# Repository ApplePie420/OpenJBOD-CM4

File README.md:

# Raspberry Pi CM4 OpenJBOD Controller

This project is heavily inspired by the work of [TheGuyDanish](https://github.com/openjbod/rp2040), specifically his [OpenJBOD](https://github.com/OpenJBOD) thingamajig.

It aims to provide much more "hackable" and robust way to to what OpenJBOD aims to do.

You can preview the schematics [in .pdf here](docs/CM4_JBOD_Control_Board.pdf)

## Images

# KiCAD libraries

Since I am not sure how to properly export my global libraries to the project, and I am too lazy to be bothered by changing the references individually, I have provided the entire "Custom_Libs" folder that I have on my computer. Some footprints or whatever might not be used in this project, you can safely ignore those. Adding this folder to library path should be enough for KiCAD to then locate all necessary symbols, footprints and 3D models. If not, you can link them manually. I might fix this sometime in the future maybe.

--- TBA ---

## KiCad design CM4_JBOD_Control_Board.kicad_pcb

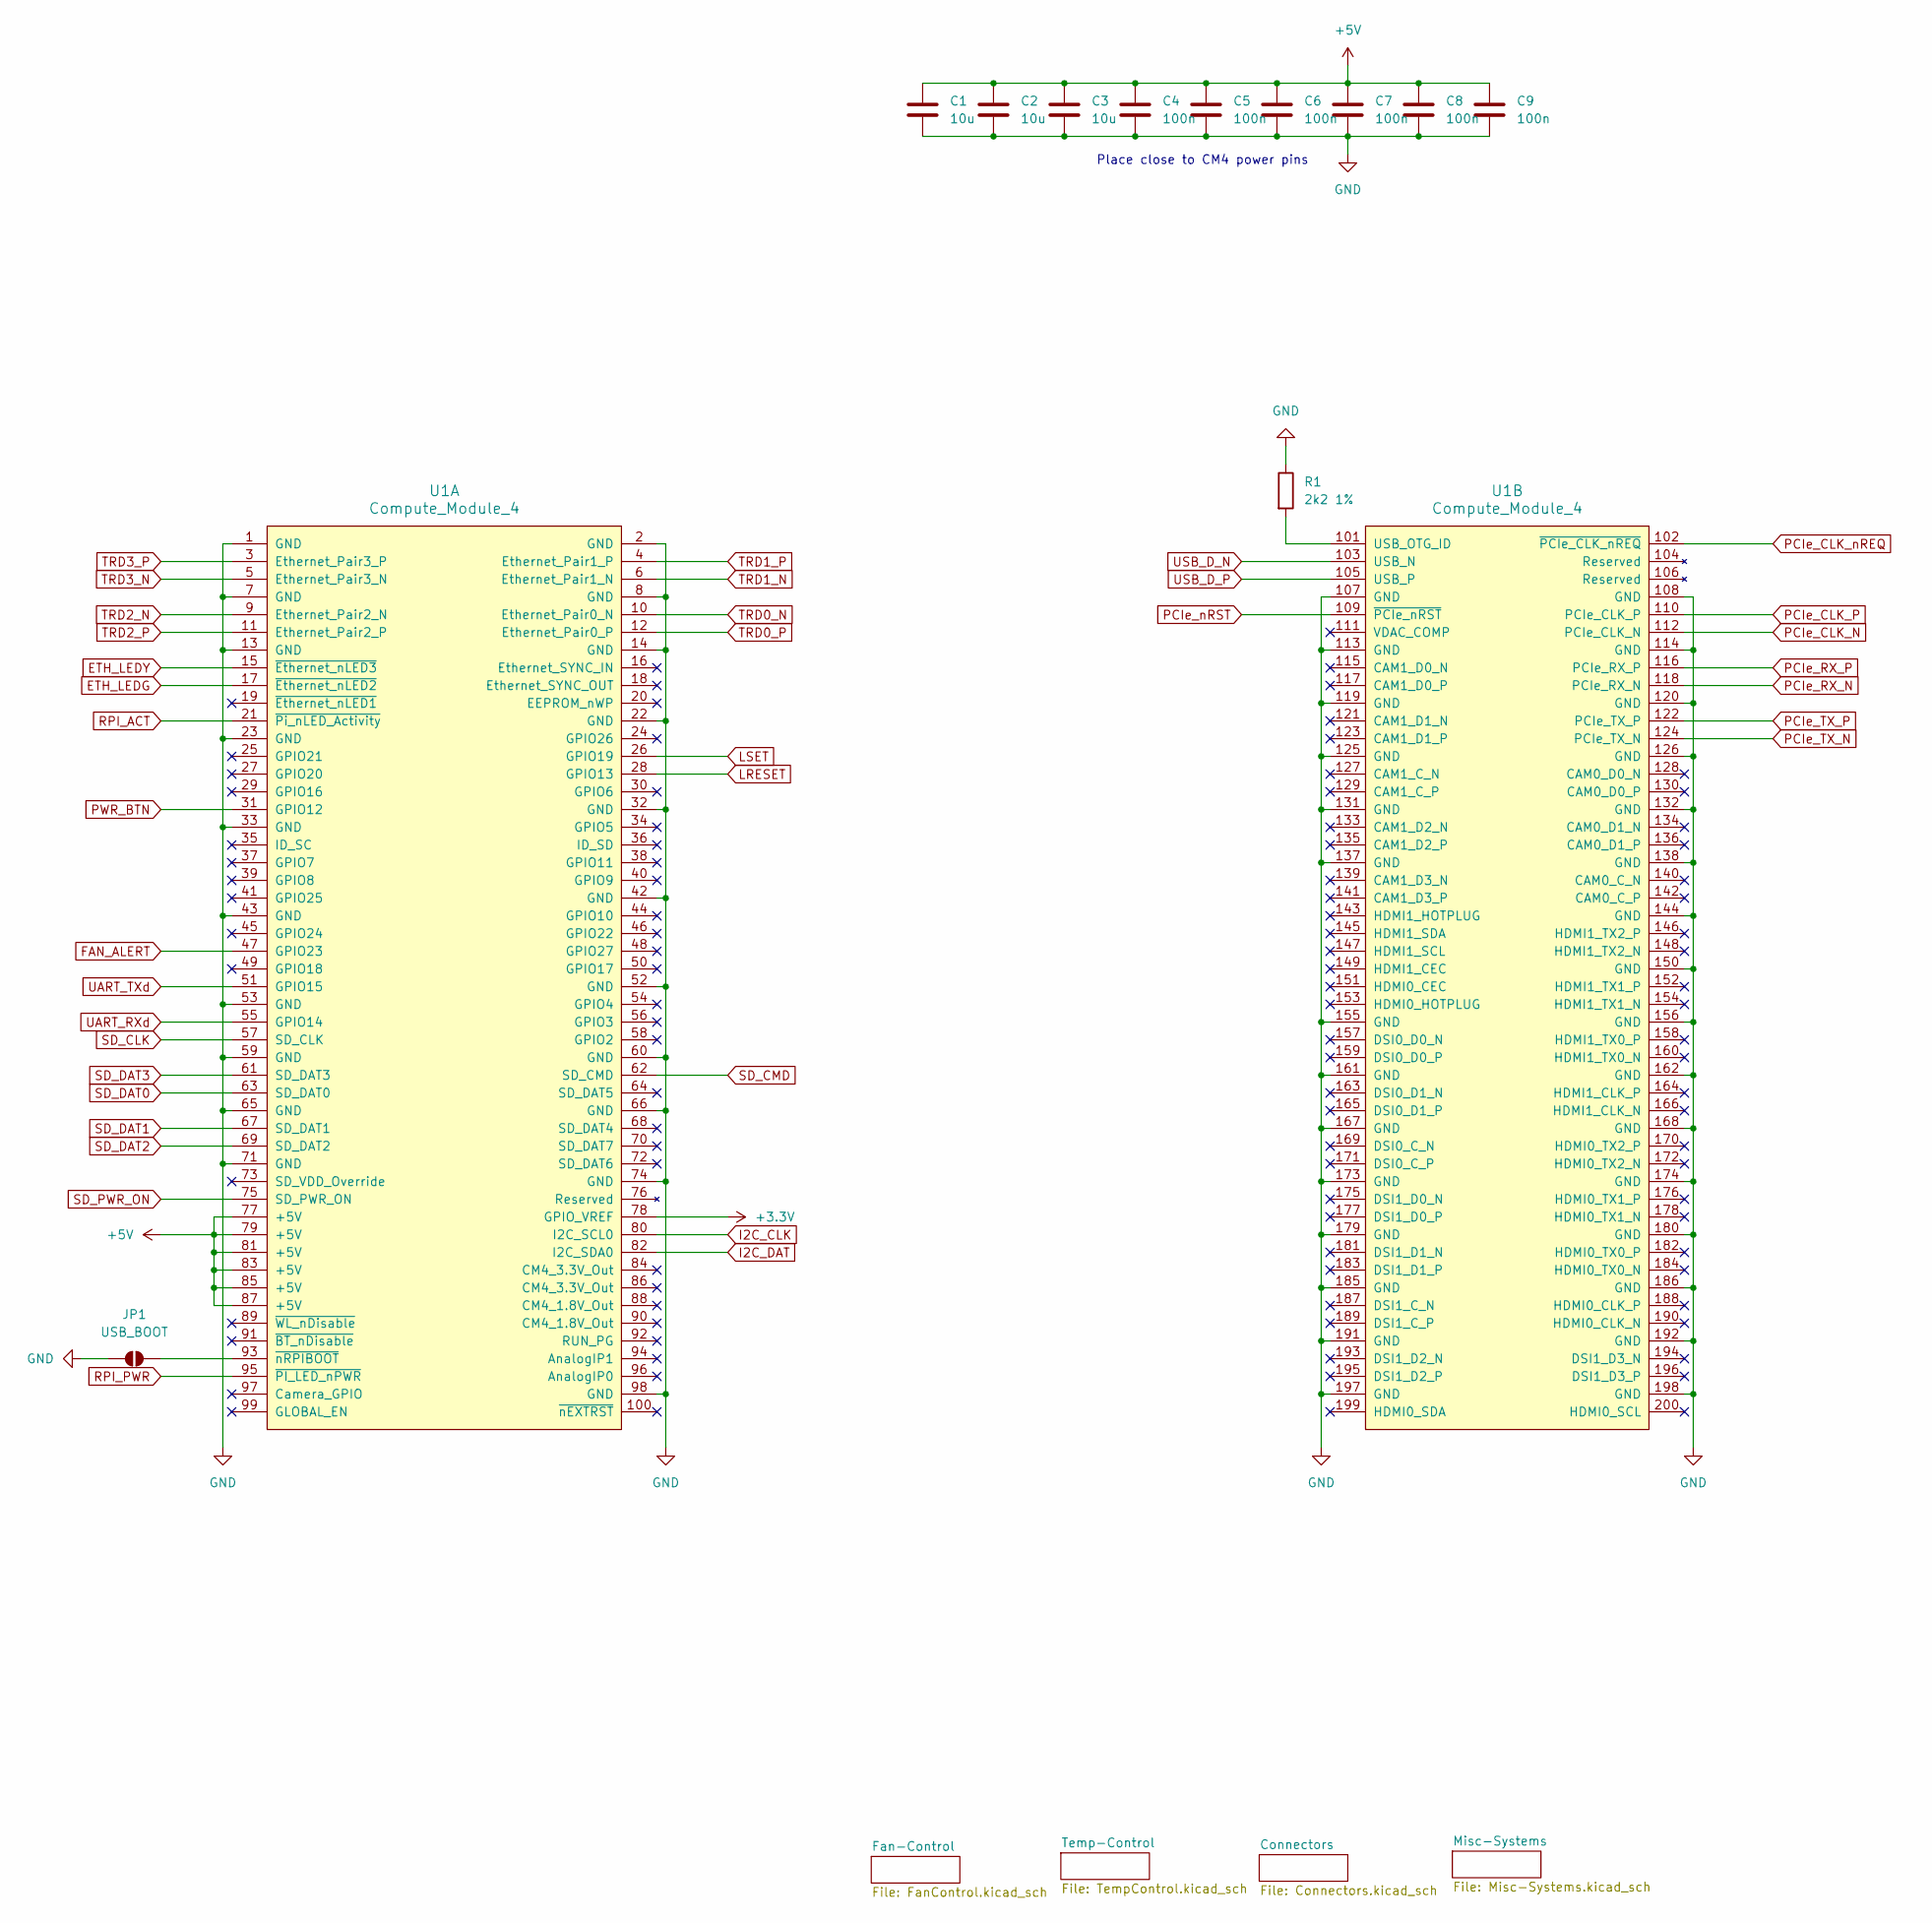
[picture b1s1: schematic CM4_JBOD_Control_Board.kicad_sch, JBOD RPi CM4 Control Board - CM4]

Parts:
C1, C2, C3: 10u; CP_EIA-3216-18_Kemet-A
C4, C5, C6, C7, C8, C9: 100n; C_0603_1608Metric
JP1: USB_BOOT; SolderJumper-2_P1.3mm_Open_TrianglePad1.0x1.5mm
R1: 2k2 1%; R_0603_1608Metric
U1: Compute_Module_4; Raspberry-Pi-4-Compute-Module

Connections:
+3.3V: U1.78 (GPIO_VREF); also elsewhere on the board
+5V: C1.1, C2.1, C3.1, C4.1, C5.1, C6.1, C7.1, C8.1, C9.1, U1.77 (+5V), U1.79 (+5V), U1.81 (+5V), U1.83 (+5V), U1.85 (+5V), U1.87 (+5V); also elsewhere on the board
ETH_LEDG: U1.17 (~Ethernet_nLED2); also elsewhere on the board
ETH_LEDY: U1.15 (~Ethernet_nLED3); also elsewhere on the board
FAN_ALERT: U1.47 (GPIO23); also elsewhere on the board
GND: C1.2, C2.2, C3.2, C4.2, C5.2, C6.2, C7.2, C8.2, C9.2, JP1.1 (A), R1.1, U1.1 (GND), U1.2 (GND), U1.7 (GND), U1.8 (GND), U1.13 (GND), U1.14 (GND), U1.22 (GND), U1.23 (GND), U1.32 (GND), U1.33 (GND), U1.42 (GND), U1.43 (GND), U1.52 (GND), U1.53 (GND), U1.59 (GND), U1.60 (GND), U1.65 (GND), U1.66 (GND), U1.71 (GND), U1.74 (GND), U1.98 (GND), U1.107 (GND), U1.108 (GND), U1.113 (GND), U1.114 (GND), U1.119 (GND), U1.120 (GND), U1.125 (GND), U1.126 (GND), U1.131 (GND), U1.132 (GND), U1.137 (GND), U1.138 (GND), U1.144 (GND), U1.150 (GND), U1.155 (GND), U1.156 (GND), U1.161 (GND), U1.162 (GND), U1.167 (GND), U1.168 (GND), U1.173 (GND), U1.174 (GND), U1.179 (GND), U1.180 (GND), U1.185 (GND), U1.186 (GND), U1.191 (GND), U1.192 (GND), U1.197 (GND), U1.198 (GND); also elsewhere on the board
I2C_CLK: U1.80 (I2C_SCL0); also elsewhere on the board
I2C_DAT: U1.82 (I2C_SDA0); also elsewhere on the board
LRESET: U1.28 (GPIO13); also elsewhere on the board
LSET: U1.26 (GPIO19); also elsewhere on the board
unnamed: JP1.2 (B), U1.93 (~nRPIBOOT)
unnamed: R1.2, U1.101 (USB_OTG_ID)
PCIe_CLK_N: U1.112 (PCIe_CLK_N); also elsewhere on the board
PCIe_CLK_P: U1.110 (PCIe_CLK_P); also elsewhere on the board
PCIe_CLK_nREQ: U1.102 (~PCIe_CLK_nREQ); also elsewhere on the board
PCIe_RX_N: U1.118 (PCIe_RX_N); also elsewhere on the board
PCIe_RX_P: U1.116 (PCIe_RX_P); also elsewhere on the board
PCIe_TX_N: U1.124 (PCIe_TX_N); also elsewhere on the board
PCIe_TX_P: U1.122 (PCIe_TX_P); also elsewhere on the board
PCIe_nRST: U1.109 (~PCIe_nRST); also elsewhere on the board
PWR_BTN: U1.31 (GPIO12); also elsewhere on the board
RPI_ACT: U1.21 (~Pi_nLED_Activity); also elsewhere on the board
RPI_PWR: U1.95 (~PI_LED_nPWR); also elsewhere on the board
SD_CLK: U1.57 (SD_CLK); also elsewhere on the board
SD_CMD: U1.62 (SD_CMD); also elsewhere on the board
SD_DAT0: U1.63 (SD_DAT0); also elsewhere on the board
SD_DAT1: U1.67 (SD_DAT1); also elsewhere on the board
SD_DAT2: U1.69 (SD_DAT2); also elsewhere on the board
SD_DAT3: U1.61 (SD_DAT3); also elsewhere on the board
SD_PWR_ON: U1.75 (SD_PWR_ON); also elsewhere on the board
TRD0_N: U1.10 (Ethernet_Pair0_N); also elsewhere on the board
TRD0_P: U1.12 (Ethernet_Pair0_P); also elsewhere on the board
TRD1_N: U1.6 (Ethernet_Pair1_N); also elsewhere on the board
TRD1_P: U1.4 (Ethernet_Pair1_P); also elsewhere on the board
TRD2_N: U1.9 (Ethernet_Pair2_N); also elsewhere on the board
TRD2_P: U1.11 (Ethernet_Pair2_P); also elsewhere on the board
TRD3_N: U1.5 (Ethernet_Pair3_N); also elsewhere on the board
TRD3_P: U1.3 (Ethernet_Pair3_P); also elsewhere on the board
UART_RXd: U1.55 (GPIO14); also elsewhere on the board
UART_TXd: U1.51 (GPIO15); also elsewhere on the board
USB_D_N: U1.103 (USB_N); also elsewhere on the board
USB_D_P: U1.105 (USB_P); also elsewhere on the board

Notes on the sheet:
Place close to CM4 power pins

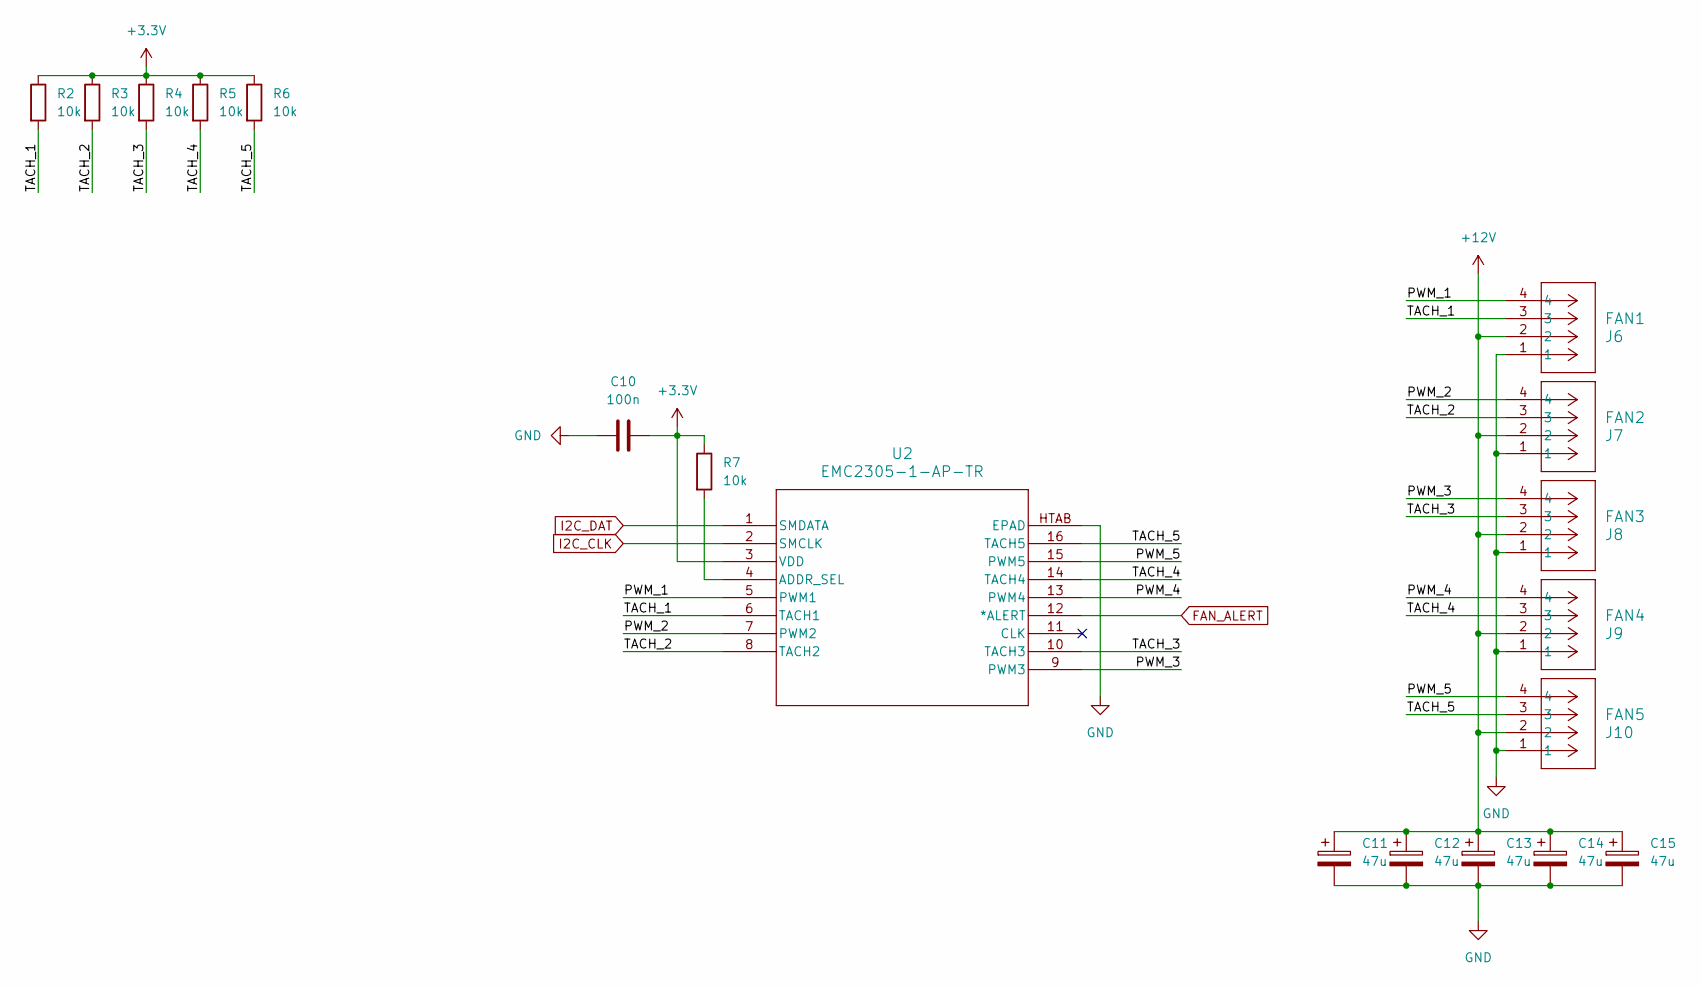
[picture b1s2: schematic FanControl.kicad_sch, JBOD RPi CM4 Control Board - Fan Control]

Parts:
C10: 100n; C_0603_1608Metric
C11, C12, C13, C14, C15: 47u; CP_EIA-3216-18_Kemet-A
J6: FAN1; CONN_SD-47053-001_H10p00_MOL
J7: FAN2; CONN_SD-47053-001_H10p00_MOL
J8: FAN3; CONN_SD-47053-001_H10p00_MOL
J9: FAN4; CONN_SD-47053-001_H10p00_MOL
J10: FAN5; CONN_SD-47053-001_H10p00_MOL
R2, R3, R4, R5, R6, R7: 10k; R_0603_1608Metric
U2: EMC2305-1-AP-TR; QFN16_4x4MC_MCH

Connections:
+3.3V: C10.2, R2.1, R3.1, R4.1, R5.1, R6.1, R7.1, U2.3 (VDD); also elsewhere on the board
+12V: C11.1, C12.1, C13.1, C14.1, C15.1, J6.2, J7.2, J8.2, J9.2, J10.2; also elsewhere on the board
/Fan-Control/PWM_1: J6.4, U2.5 (PWM1)
/Fan-Control/PWM_2: J7.4, U2.7 (PWM2)
/Fan-Control/PWM_3: J8.4, U2.9 (PWM3)
/Fan-Control/PWM_4: J9.4, U2.13 (PWM4)
/Fan-Control/PWM_5: J10.4, U2.15 (PWM5)
/Fan-Control/TACH_1: J6.3, R2.2, U2.6 (TACH1)
/Fan-Control/TACH_2: J7.3, R3.2, U2.8 (TACH2)
/Fan-Control/TACH_3: J8.3, R4.2, U2.10 (TACH3)
/Fan-Control/TACH_4: J9.3, R5.2, U2.14 (TACH4)
/Fan-Control/TACH_5: J10.3, R6.2, U2.16 (TACH5)
FAN_ALERT: U2.12 (*ALERT); also elsewhere on the board
GND: C10.1, C11.2, C12.2, C13.2, C14.2, C15.2, J6.1, J7.1, J8.1, J9.1, J10.1, U2.17, U2.HTAB (EPAD); also elsewhere on the board
I2C_CLK: U2.2 (SMCLK); also elsewhere on the board
I2C_DAT: U2.1 (SMDATA); also elsewhere on the board
unnamed: R7.2, U2.4 (ADDR_SEL)

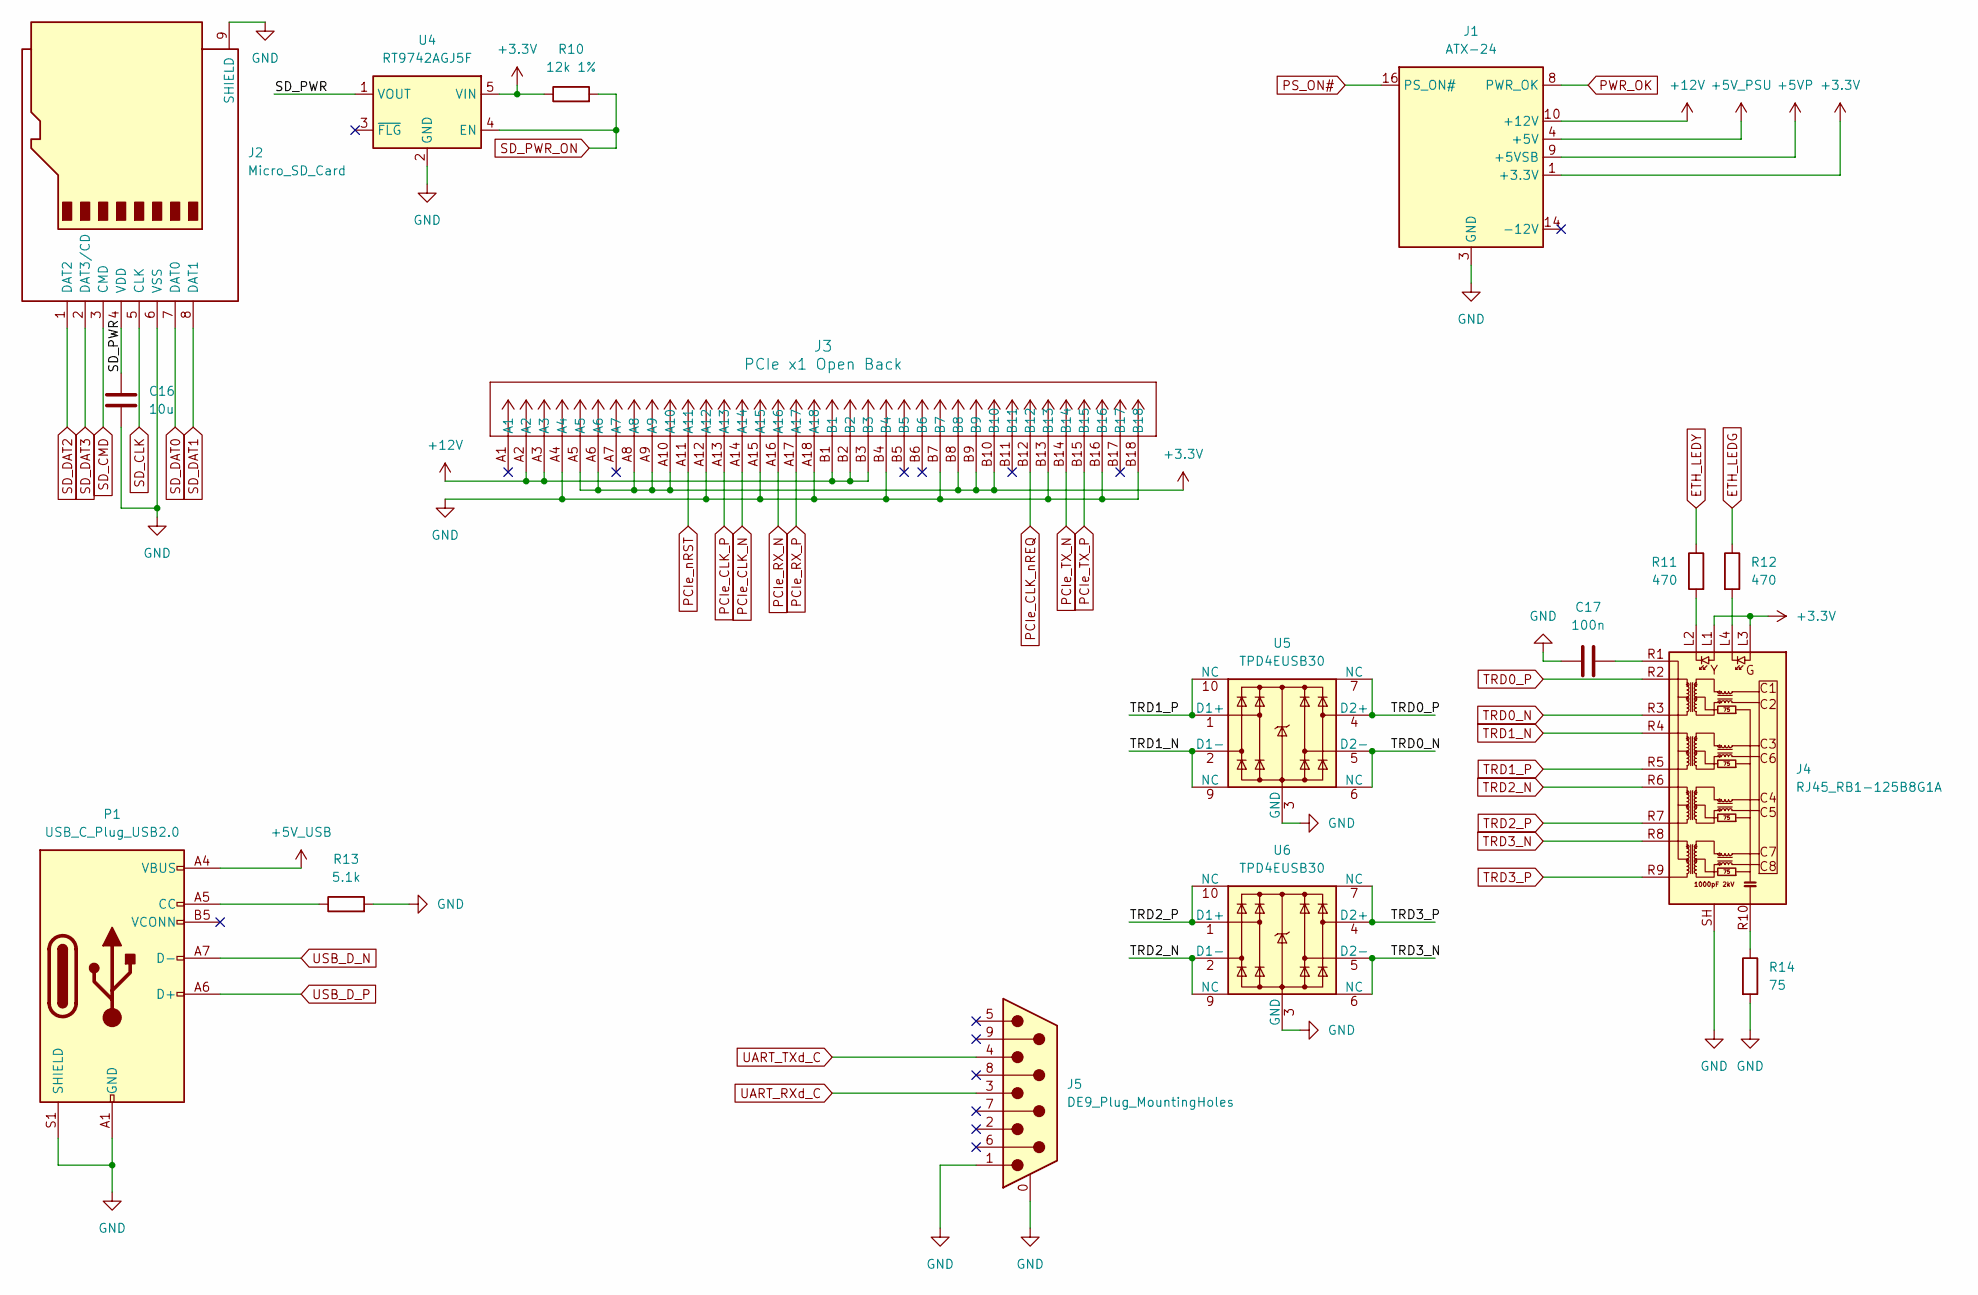
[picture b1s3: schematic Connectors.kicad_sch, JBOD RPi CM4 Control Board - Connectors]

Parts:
C16: 10u; CP_EIA-3216-18_Kemet-A
C17: 100n; C_0603_1608Metric
J1: ATX-24; Molex_Mini-Fit_Jr_5566-24A_2x12_P4.20mm_Vertical
J2: Micro_SD_Card; microSD_HC_Molex_104031-0811
J3: PCIe x1 Open Back; CONN36_6-1734774-7_PCIe_x1
J4: RJ45_RB1-125B8G1A; RJ45_UDE_RB1-125B8G1A
J5: DE9_Plug_MountingHoles; DSUB-9_Male_Horizontal_P2.77x2.84mm_EdgePinOffset4.94mm_Hou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
P1: USB_C_Plug_USB2.0; USB_C_Receptacle_GCT_USB4105-xx-A_16P_TopMnt_Horizontal
R10: 12k 1%; R_0603_1608Metric
R11, R12: 470; R_0603_1608Metric
R13: 5.1k; R_0603_1608Metric
R14: 75; R_0603_1608Metric
U4: RT9742AGJ5F; TSOT-23-5
U5, U6: TPD4EUSB30; USON-10_2.5x1.0mm_P0.5mm

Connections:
+3.3V: J1.1 (+3.3V), J1.2 (+3.3V), J1.12 (+3.3V), J1.13 (+3.3V), J3.A5, J3.A6, J3.A8, J3.A9, J3.A10, J3.B8, J3.B9, J3.B10, J4.L1, J4.L3, R10.1, U4.5 (VIN); also elsewhere on the board
+5VP: J1.9 (+5VSB)
+5V_PSU: J1.4 (+5V), J1.6 (+5V), J1.21 (+5V), J1.22 (+5V), J1.23 (+5V); also elsewhere on the board
+5V_USB: P1.A4 (VBUS), P1.A9 (VBUS), P1.B4 (VBUS), P1.B9 (VBUS); also elsewhere on the board
+12V: J1.10 (+12V), J1.11 (+12V), J3.A2, J3.A3, J3.B1, J3.B2, J3.B3; also elsewhere on the board
/Connectors/SD_PWR: C16.2, J2.4 (VDD), U4.1 (VOUT)
ETH_LEDG: R12.1; also elsewhere on the board
ETH_LEDY: R11.1; also elsewhere on the board
GND: C16.1, C17.2, J1.3 (GND), J1.5 (GND), J1.7 (GND), J1.15 (GND), J1.17 (GND), J1.18 (GND), J1.19 (GND), J1.24 (GND), J2.6 (VSS), J2.9 (SHIELD), J3.A4, J3.A12, J3.A15, J3.A18, J3.B4, J3.B7, J3.B13, J3.B16, J3.B18, J4.SH, J5.0 (PAD), J5.1, P1.A1 (GND), P1.A12 (GND), P1.B1 (GND), P1.B12 (GND), P1.S1 (SHIELD), R13.2, R14.2, U4.2 (GND), U5.3 (GND), U5.8 (GND), U6.3 (GND), U6.8 (GND); also elsewhere on the board
unnamed: C17.1, J4.R1 (CT)
unnamed: J4.R10 (GND), R14.1
unnamed: J4.L2, R11.2
unnamed: J4.L4, R12.2
unnamed: P1.A5 (CC), R13.1
PCIe_CLK_N: J3.A14; also elsewhere on the board
PCIe_CLK_P: J3.A13; also elsewhere on the board
PCIe_CLK_nREQ: J3.B12; also elsewhere on the board
PCIe_RX_N: J3.A16; also elsewhere on the board
PCIe_RX_P: J3.A17; also elsewhere on the board
PCIe_TX_N: J3.B14; also elsewhere on the board
PCIe_TX_P: J3.B15; also elsewhere on the board
PCIe_nRST: J3.A11; also elsewhere on the board
PS_ON#: J1.16 (PS_ON#); also elsewhere on the board
PWR_OK: J1.8 (PWR_OK); also elsewhere on the board
SD_CLK: J2.5 (CLK); also elsewhere on the board
SD_CMD: J2.3 (CMD); also elsewhere on the board
SD_DAT0: J2.7 (DAT0); also elsewhere on the board
SD_DAT1: J2.8 (DAT1); also elsewhere on the board
SD_DAT2: J2.1 (DAT2); also elsewhere on the board
SD_DAT3: J2.2 (DAT3/CD); also elsewhere on the board
SD_PWR_ON: R10.2, U4.4 (EN); also elsewhere on the board
TRD0_N: J4.R3 (TD1-), U5.5 (D2-), U5.6 (NC); also elsewhere on the board
TRD0_P: J4.R2 (TD1+), U5.4 (D2+), U5.7 (NC); also elsewhere on the board
TRD1_N: J4.R4 (TD2+), U5.2 (D1-), U5.9 (NC); also elsewhere on the board
TRD1_P: J4.R5 (TD2-), U5.1 (D1+), U5.10 (NC); also elsewhere on the board
TRD2_N: J4.R6 (TD3+), U6.2 (D1-), U6.9 (NC); also elsewhere on the board
TRD2_P: J4.R7 (TD3-), U6.1 (D1+), U6.10 (NC); also elsewhere on the board
TRD3_N: J4.R8 (TD4+), U6.5 (D2-), U6.6 (NC); also elsewhere on the board
TRD3_P: J4.R9 (TD4-), U6.4 (D2+), U6.7 (NC); also elsewhere on the board
UART_RXd_C: J5.3; also elsewhere on the board
UART_TXd_C: J5.4; also elsewhere on the board
USB_D_N: P1.A7 (D-); also elsewhere on the board
USB_D_P: P1.A6 (D+); also elsewhere on the board

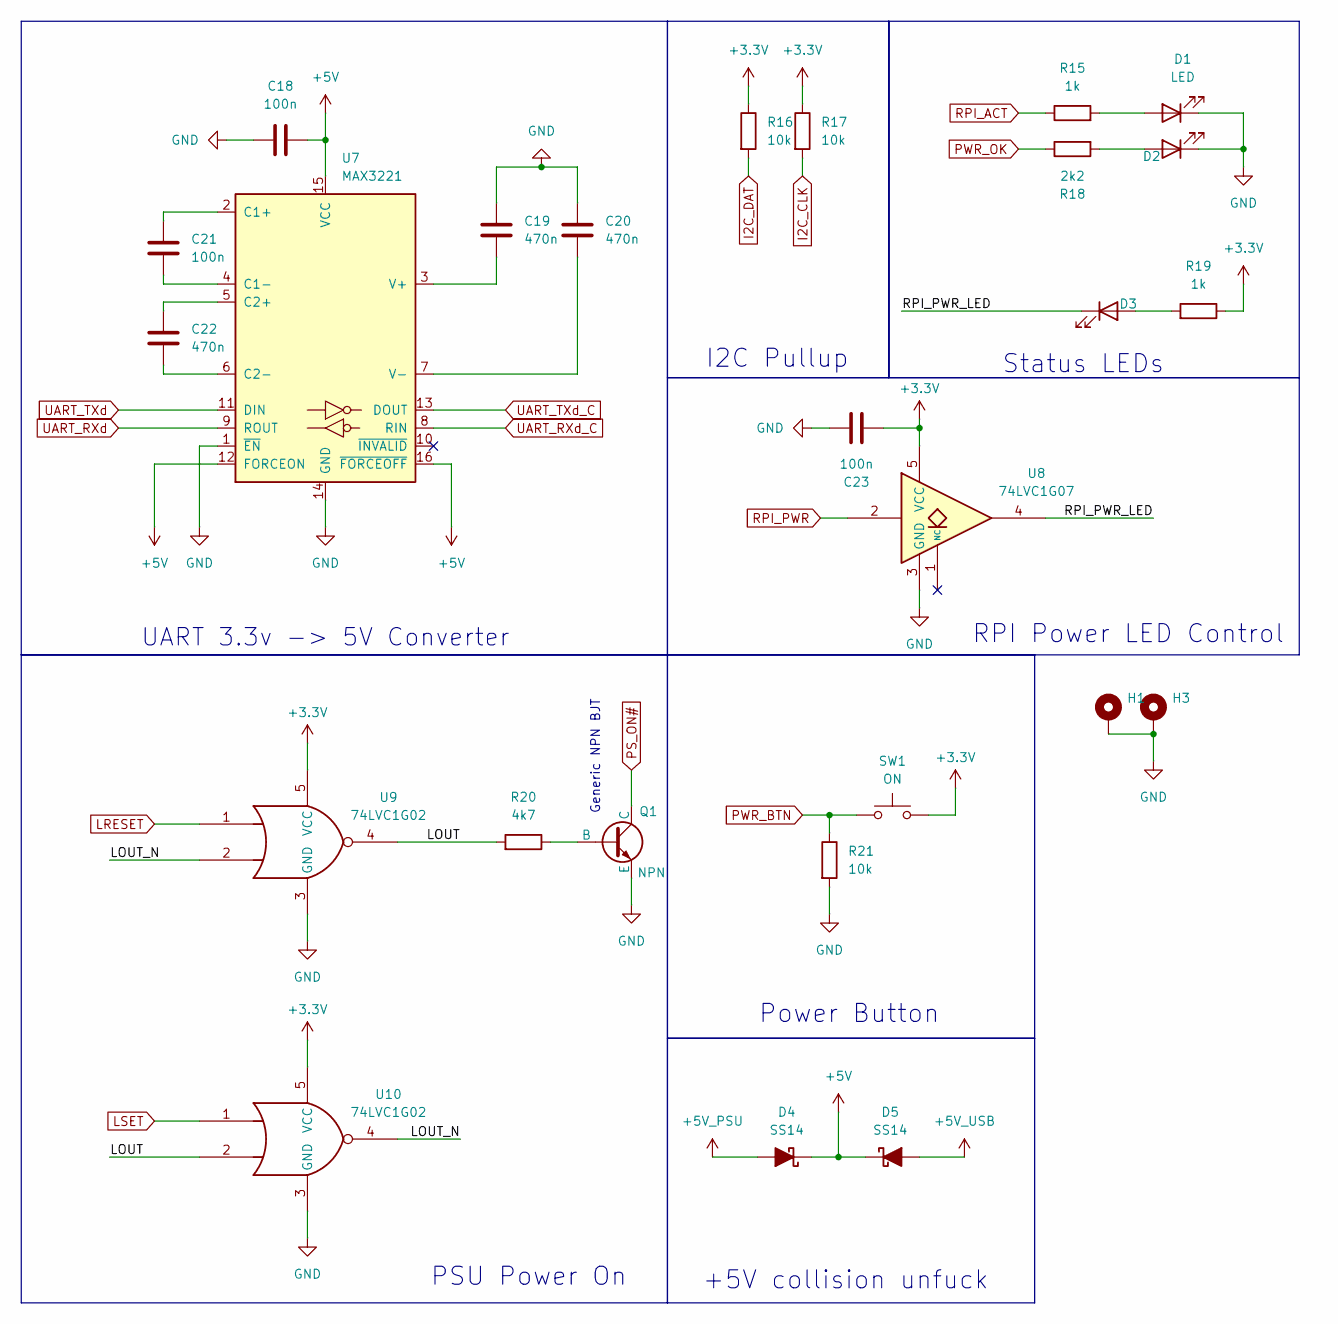
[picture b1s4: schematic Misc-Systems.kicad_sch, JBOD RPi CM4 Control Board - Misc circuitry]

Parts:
C18, C21, C23: 100n; C_0603_1608Metric
C19, C20, C22: 470n; C_0603_1608Metric
D1, D2, D3: LED; LED_0603_1608Metric
D4, D5: SS14; D_SMA
H1, H3: MountingHole_Pad; MountingHole_4mm_Pad_TopBottom
Q1: NPN; SOT-23
R15, R19: 1k; R_0603_1608Metric
R16, R17, R21: 10k; R_0603_1608Metric
R18: 2k2; R_0603_1608Metric
R20: 4k7; R_0603_1608Metric
SW1: ON; SW_SPST_B3U-3000P
U7: MAX3221; TSSOP-16_4.4x5mm_P0.65mm
U8: 74LVC1G07; SOT-23-5
U9, U10: 74LVC1G02; SOT-23-5

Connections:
+3.3V: C23.2, R16.1, R17.1, R19.1, SW1.2, U8.5 (VCC), U9.5 (VCC), U10.5 (VCC); also elsewhere on the board
+5V: C18.2, D4.1 (K), D5.1 (K), U7.12 (FORCEON), U7.15 (VCC), U7.16 (~FORCEOFF); also elsewhere on the board
+5V_PSU: D4.2 (A); also elsewhere on the board
+5V_USB: D5.2 (A); also elsewhere on the board
/Misc-Systems/LOUT: R20.2, U9.4, U10.2
/Misc-Systems/LOUT_N: U9.2, U10.4
/Misc-Systems/RPI_PWR_LED: D3.1 (K), U8.4
GND: C18.1, C19.2, C20.2, C23.1, D1.1 (K), D2.1 (K), H1.1, H3.1, Q1.3 (E), R21.2, U7.1 (~EN), U7.14 (GND), U8.3 (GND), U9.3 (GND), U10.3 (GND); also elsewhere on the board
I2C_CLK: R17.2; also elsewhere on the board
I2C_DAT: R16.2; also elsewhere on the board
LRESET: U9.1; also elsewhere on the board
LSET: U10.1; also elsewhere on the board
unnamed: D1.2 (A), R15.2
unnamed: D2.2 (A), R18.2
unnamed: D3.2 (A), R19.2
unnamed: Q1.2 (B), R20.1
unnamed: C21.2, U7.2 (C1+)
unnamed: C21.1, U7.4 (C1-)
unnamed: C22.2, U7.5 (C2+)
unnamed: C22.1, U7.6 (C2-)
unnamed: C19.1, U7.3 (V+)
unnamed: C20.1, U7.7 (V-)
PS_ON#: Q1.1 (C); also elsewhere on the board
PWR_BTN: R21.1, SW1.1; also elsewhere on the board
PWR_OK: R18.1; also elsewhere on the board
RPI_ACT: R15.1; also elsewhere on the board
RPI_PWR: U8.2; also elsewhere on the board
UART_RXd: U7.9 (ROUT); also elsewhere on the board
UART_RXd_C: U7.8 (RIN); also elsewhere on the board
UART_TXd: U7.11 (DIN); also elsewhere on the board
UART_TXd_C: U7.13 (DOUT); also elsewhere on the board

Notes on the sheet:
PSU Power On
Status LEDs
Generic NPN BJT
I2C Pullup
UART 3.3v -> 5V Converter
Power Button
+5V collision unfuck
RPI Power LED Control

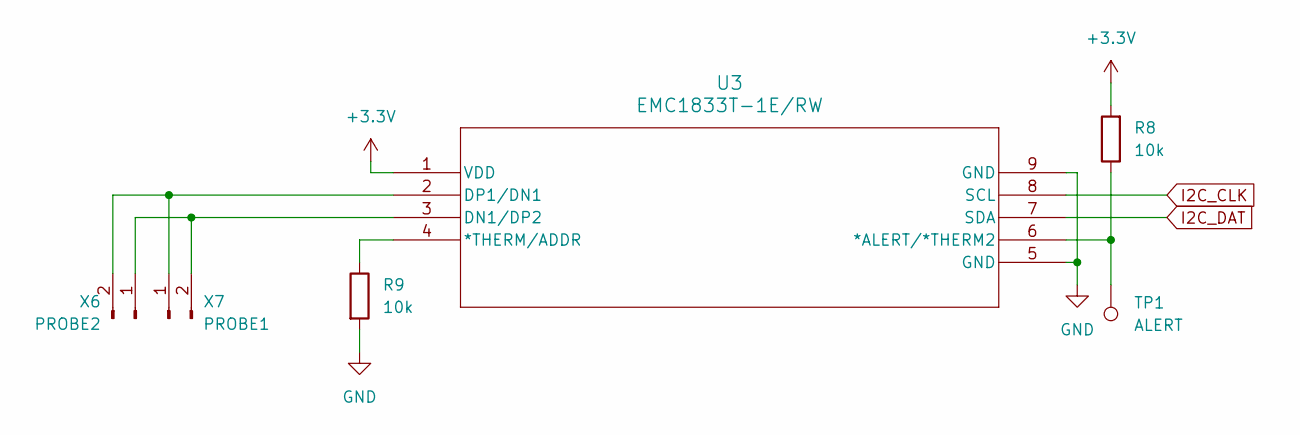
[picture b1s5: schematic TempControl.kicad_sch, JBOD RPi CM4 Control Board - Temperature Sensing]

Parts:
R8, R9: 10k; R_0603_1608Metric
TP1: ALERT; TestPoint_Pad_D1.0mm
U3: EMC1833T-1E/RW; WDFN8_RW_MCH
X6: PROBE2; JST_EH_B2B-EH-A_1x02_P2.50mm_Vertical
X7: PROBE1; JST_EH_B2B-EH-A_1x02_P2.50mm_Vertical

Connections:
+3.3V: R8.2, U3.1 (VDD); also elsewhere on the board
GND: R9.2, U3.5 (GND), U3.9 (GND); also elsewhere on the board
I2C_CLK: U3.8 (SCL); also elsewhere on the board
I2C_DAT: U3.7 (SDA); also elsewhere on the board
unnamed: R8.1, TP1.1, U3.6 (*ALERT/*THERM2)
unnamed: R9.1, U3.4 (*THERM/ADDR)
unnamed: U3.3 (DN1/DP2), X6.1, X7.2
unnamed: U3.2 (DP1/DN1), X6.2, X7.1

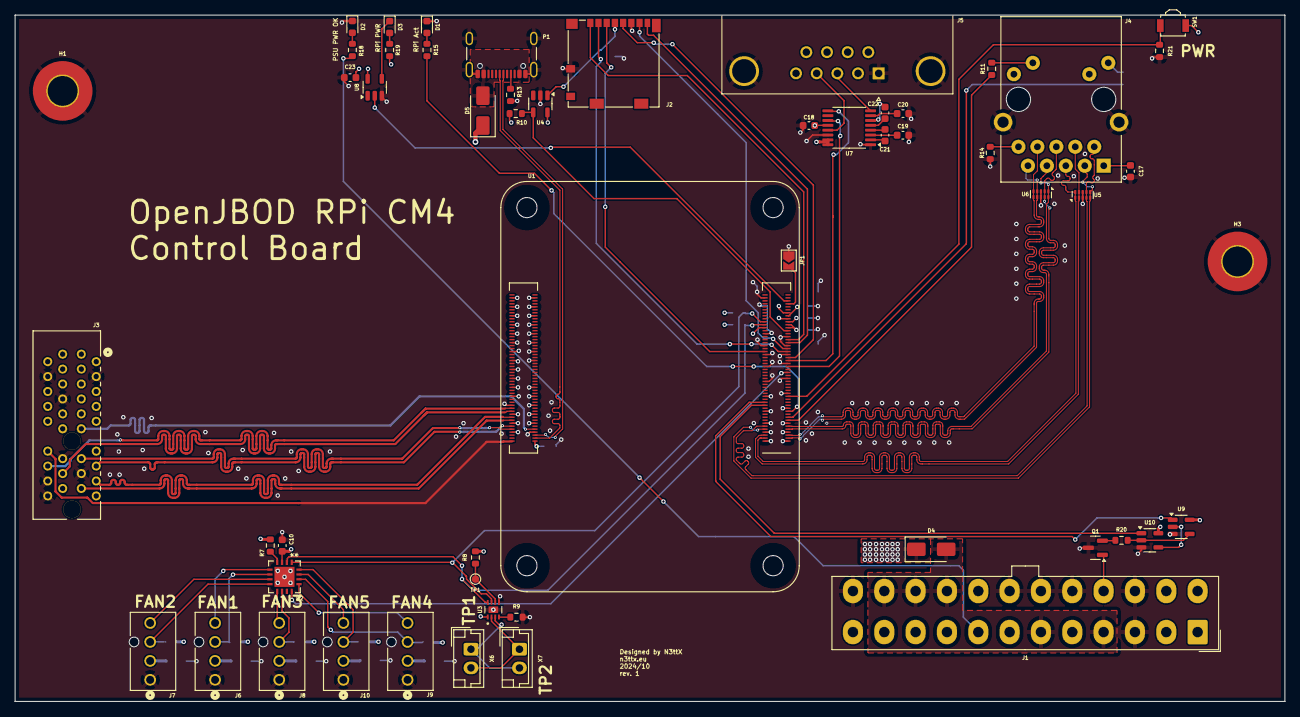
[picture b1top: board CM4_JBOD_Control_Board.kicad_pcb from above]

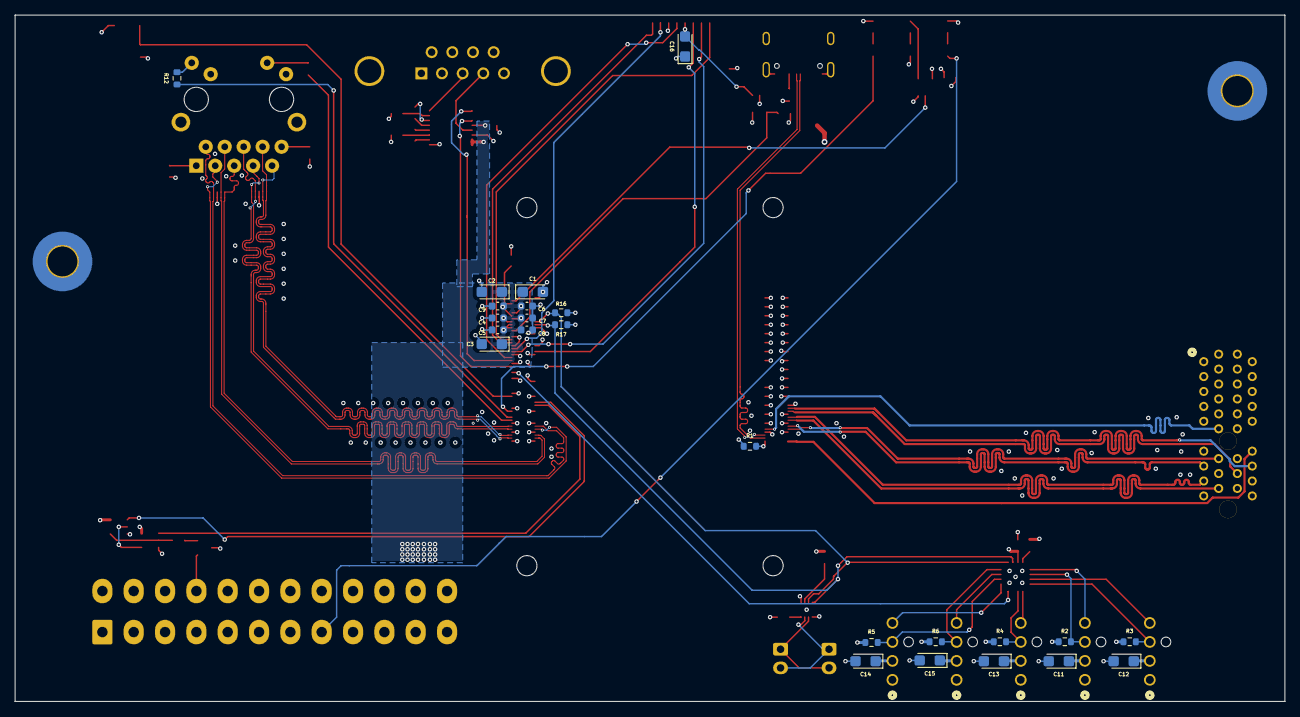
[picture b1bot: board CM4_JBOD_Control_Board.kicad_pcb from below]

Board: 4 copper layers, 170.2 x 92.0 mm, 78 parts (24 on the bottom side), 83 nets.

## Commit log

2024-10-06 rev. 1
2024-10-06 added README
2024-10-06 Images, schematics in pdf, readme update
